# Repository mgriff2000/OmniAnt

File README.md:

# OmniAnt
Repo for the KiCad project for OmniAnt

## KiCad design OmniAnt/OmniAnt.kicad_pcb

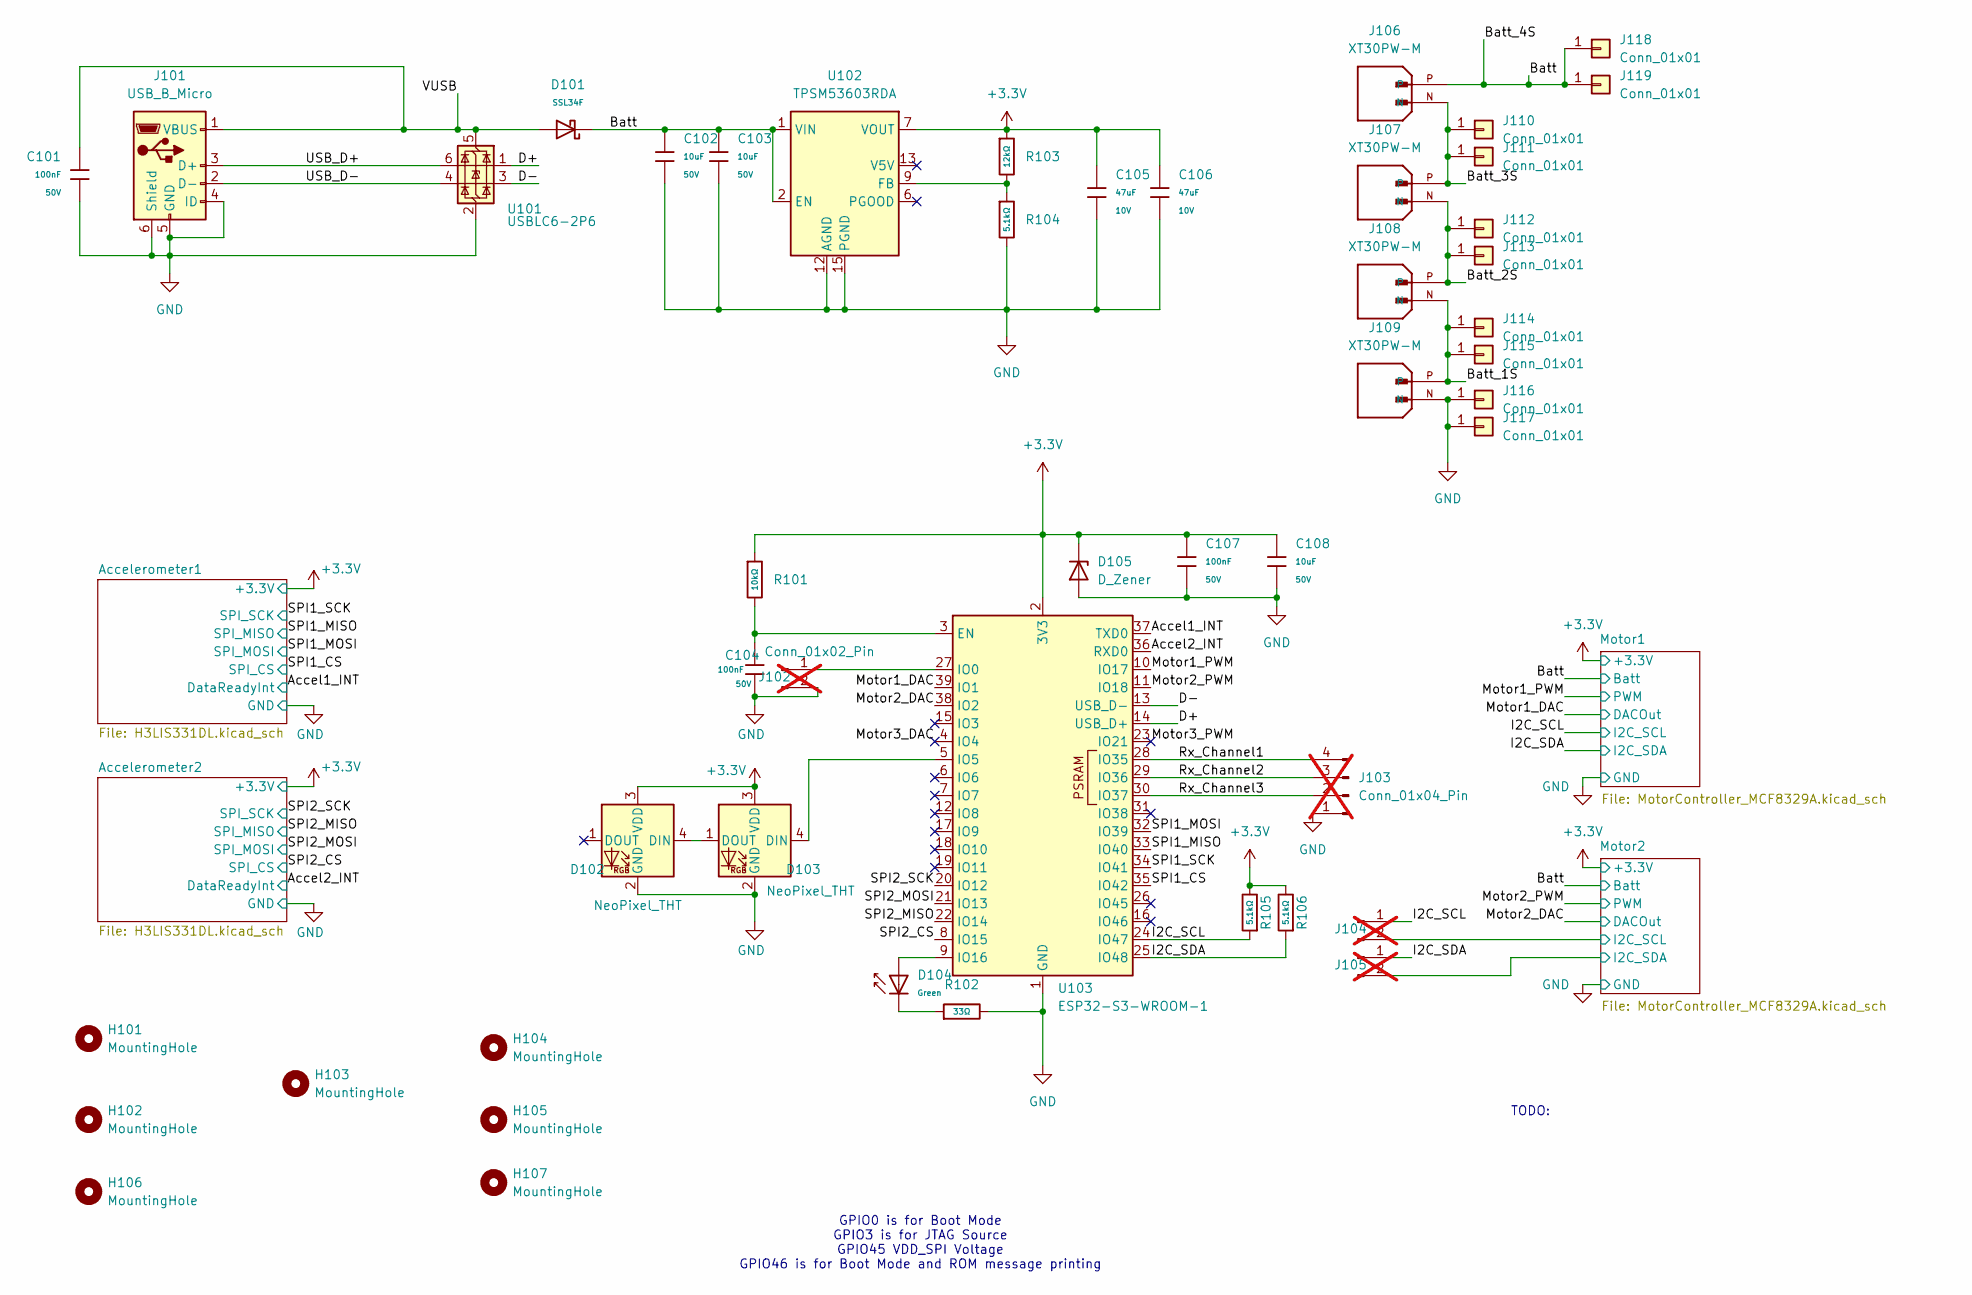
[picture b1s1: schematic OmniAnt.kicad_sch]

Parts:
C101, C104, C107: 100nF; C_0603; Voltage Rated 50V; Tolerance ±10%; Part CC0603KRX7R9BB104; LCSC C14663
C102, C103, C108: 10uF; C_0805; Voltage Rated 50V; Tolerance ±10%; Part GRM21BR61H106KE43L; LCSC C440198
C105, C106: 47uF; C_1206; Voltage Rated 10V; Tolerance ±20%; Part CL31A476MPHNNNE; LCSC C96123
D101: SSL34F; D_SMAF; Part SSL34F; LCSC C28646282
D102, D103: NeoPixel_THT; LED_D5.0mm-4_RGB
D104: Green; D_0805; Part KT-0805G; LCSC C2297
D105: D_Zener; D_SOD-123FL; Manufacturer Part Number SMF3.3; LCSC C2649858
H101, H102, H104, H105, H106, H107: MountingHole; MountingHole_3mm
H103: MountingHole; MountingHole_4.3mm_M4_DIN965
J101: USB_B_Micro; USB_Micro-B_Molex-105017-0001; LCSC C136000
J102, J104, J105: Conn_01x02_Pin; PinHeader_1x02_P1.27mm_Vertical; not fitted
J103: Conn_01x04_Pin; PinHeader_1x04_P2.54mm_Vertical; not fitted
J106, J107, J108, J109: XT30PW-M; AMASS_XT30PW-M; PARTREV 1.2; LCSC C431092
J110, J111, J112, J113, J114, J115, J116, J117, J118, J119: Conn_01x01; SolderWire-1.5sqmm_1x01_D1.7mm_OD3mm
R101: 10kΩ; R_0402; Overload Voltage (Max) 50V; Tolerance ±1%; Part 0402WGF1002TCE; LCSC C25744
R102: 33Ω; R_0402; Overload Voltage (Max) 50V; Tolerance ±1%; Part 0402WGF330JTCE; LCSC C25105
R103: 12kΩ; R_0402; Overload Voltage (Max) 50V; Tolerance ±1%; Part 0402WGF1202TCE; LCSC C25752
R104, R105, R106: 5.1kΩ; R_0402; Overload Voltage (Max) 50V; Tolerance ±1%; Part 0402WGF5101TCE; LCSC C25905
U101: USBLC6-2P6; SOT-666; LCSC C15999
U102: TPSM53603RDA; Texas_B3QFN-14-1EP_5x5.5mm_P0.65mm_ThermalVia; LCSC C2860943
U103: ESP32-S3-WROOM-1; LCSC C2913197

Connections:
+3.3V: C105.1, C106.1, C107.1, C108.1, D102.3 (VDD), D103.3 (VDD), D105.1 (K), R101.1, R103.1, R105.2, R106.2, U102.7 (VOUT), U102.8 (VOUT), U103.2 (3V3); also elsewhere on the board
/Accel1_INT: U103.37 (TXD0); also elsewhere on the board
/Accel2_INT: U103.36 (RXD0); also elsewhere on the board
/Batt: C102.1, C103.1, D101.1, J106.P, J118.1, J119.1, U102.1 (VIN), U102.2 (EN), U102.14 (VIN); also elsewhere on the board
/Batt_1S: J108.N, J109.P, J114.1, J115.1
/Batt_2S: J107.N, J108.P, J112.1, J113.1
/Batt_3S: J106.N, J107.P, J110.1, J111.1
/D+: U101.1 (I/O1), U103.14 (USB_D+)
/D-: U101.3 (I/O2), U103.13 (USB_D-)
/I2C_SCL: J104.1, R105.1, U103.24 (IO47); also elsewhere on the board
/I2C_SDA: J105.1, R106.1, U103.25 (IO48); also elsewhere on the board
/Motor1_DAC: U103.39 (IO1); also elsewhere on the board
/Motor1_PWM: U103.10 (IO17); also elsewhere on the board
/Motor2/I2C_SCL: J104.2; also elsewhere on the board
/Motor2/I2C_SDA: J105.2; also elsewhere on the board
/Motor2_DAC: U103.38 (IO2); also elsewhere on the board
/Motor2_PWM: U103.11 (IO18); also elsewhere on the board
/Motor3_DAC: U103.4 (IO4)
/Motor3_PWM: U103.23 (IO21)
/Rx_Channel1: J103.4, U103.28 (IO35)
/Rx_Channel2: J103.3, U103.29 (IO36)
/Rx_Channel3: J103.2, U103.30 (IO37)
/SPI1_CS: U103.35 (IO42); also elsewhere on the board
/SPI1_MISO: U103.33 (IO40); also elsewhere on the board
/SPI1_MOSI: U103.32 (IO39); also elsewhere on the board
/SPI1_SCK: U103.34 (IO41); also elsewhere on the board
/SPI2_CS: U103.8 (IO15); also elsewhere on the board
/SPI2_MISO: U103.22 (IO14); also elsewhere on the board
/SPI2_MOSI: U103.21 (IO13); also elsewhere on the board
/SPI2_SCK: U103.20 (IO12); also elsewhere on the board
/USB_D+: J101.3 (D+), U101.6 (I/O1)
/USB_D-: J101.2 (D-), U101.4 (I/O2)
/VUSB: C101.1, D101.2, J101.1 (VBUS), U101.5 (VBUS)
GND: C101.2, C102.2, C103.2, C104.2, C105.2, C106.2, C107.2, C108.2, D102.2 (GND), D103.2 (GND), D105.2 (A), J101.4 (ID), J101.5 (GND), J101.6 (Shield), J102.2, J103.1, J109.N, J116.1, J117.1, R102.2, R104.2, U101.2 (GND), U102.3 (PGND), U102.10 (PGND), U102.11 (PGND), U102.12 (AGND), U102.15 (PGND), U103.1 (GND), U103.40 (GND), U103.41 (GND); also elsewhere on the board
unnamed: D102.4 (DIN), D103.1 (DOUT)
unnamed: D103.4 (DIN), U103.5 (IO5)
unnamed: D104.1, R102.1
unnamed: J102.1, U103.27 (IO0)
unnamed: R103.2, R104.1, U102.9 (FB)
unnamed: C104.1, R101.2, U103.3 (EN)
unnamed: D104.2, U103.9 (IO16)

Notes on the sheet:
TODO:
GPIO0 is for Boot Mode GPIO3 is for JTAG Source GPIO45 VDD_SPI Voltage GPIO46 is for Boot Mode and ROM message printing

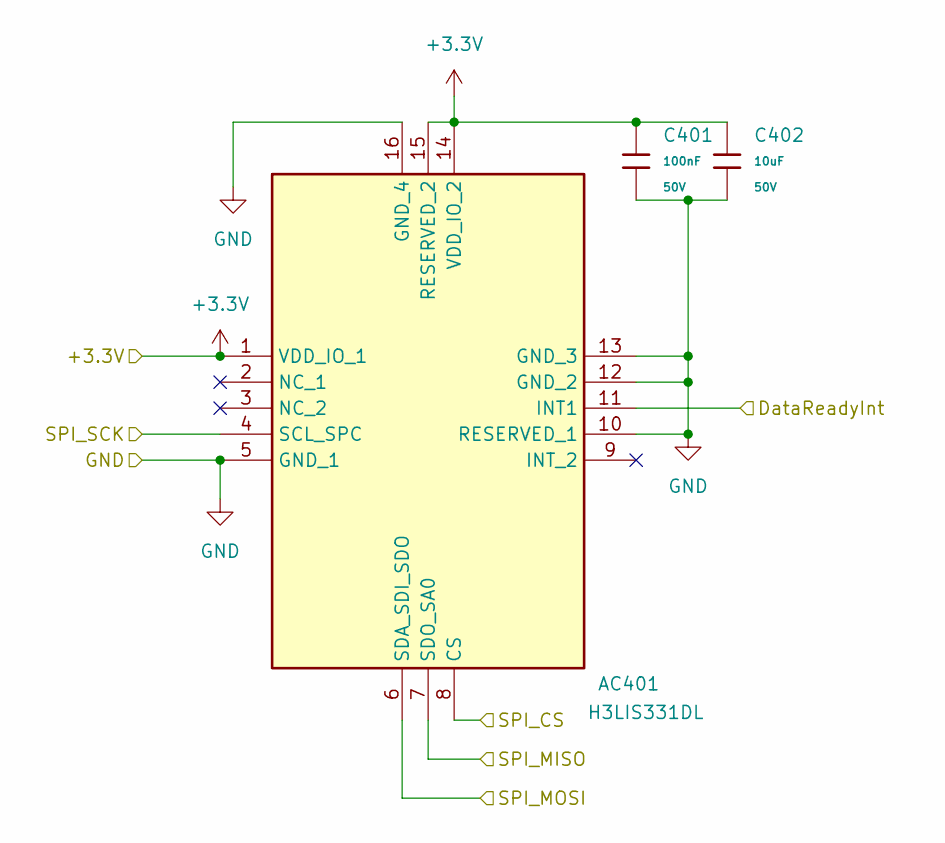
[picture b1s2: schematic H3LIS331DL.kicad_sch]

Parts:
AC401: H3LIS331DL; LIS3DHTR; Manufacturer_Part_Number H3LIS331DL; Mouser Part Number 511-H3LIS331DL
C401: 100nF; C_0603; Voltage Rated 50V; Tolerance ±10%; Part CC0603KRX7R9BB104; LCSC C14663
C402: 10uF; C_0805; Voltage Rated 50V; Tolerance ±10%; Part GRM21BR61H106KE43L; LCSC C440198

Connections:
+3.3V: AC401.1 (VDD_IO_1), AC401.14 (VDD_IO_2), AC401.15 (RESERVED_2), C401.1, C402.1; also elsewhere on the board
/Accel1_INT: AC401.11 (INT1); also elsewhere on the board
/SPI1_CS: AC401.8 (CS); also elsewhere on the board
/SPI1_MISO: AC401.7 (SDO_SA0); also elsewhere on the board
/SPI1_MOSI: AC401.6 (SDA_SDI_SDO); also elsewhere on the board
/SPI1_SCK: AC401.4 (SCL_SPC); also elsewhere on the board
GND: AC401.5 (GND_1), AC401.10 (RESERVED_1), AC401.12 (GND_2), AC401.13 (GND_3), AC401.16 (GND_4), C401.2, C402.2; also elsewhere on the board

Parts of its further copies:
AC501: H3LIS331DL; LIS3DHTR; Manufacturer_Part_Number H3LIS331DL; Mouser Part Number 511-H3LIS331DL
C501: 100nF; C_0603; Voltage Rated 50V; Tolerance ±10%; Part CC0603KRX7R9BB104; LCSC C14663
C502: 10uF; C_0805; Voltage Rated 50V; Tolerance ±10%; Part GRM21BR61H106KE43L; LCSC C440198

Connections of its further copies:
+3.3V: AC501.1 (VDD_IO_1), AC501.14 (VDD_IO_2), AC501.15 (RESERVED_2), C501.1, C502.1; also elsewhere on the board
/Accel2_INT: AC501.11 (INT1); also elsewhere on the board
/SPI2_CS: AC501.8 (CS); also elsewhere on the board
/SPI2_MISO: AC501.7 (SDO_SA0); also elsewhere on the board
/SPI2_MOSI: AC501.6 (SDA_SDI_SDO); also elsewhere on the board
/SPI2_SCK: AC501.4 (SCL_SPC); also elsewhere on the board
GND: AC501.5 (GND_1), AC501.10 (RESERVED_1), AC501.12 (GND_2), AC501.13 (GND_3), AC501.16 (GND_4), C501.2, C502.2; also elsewhere on the board

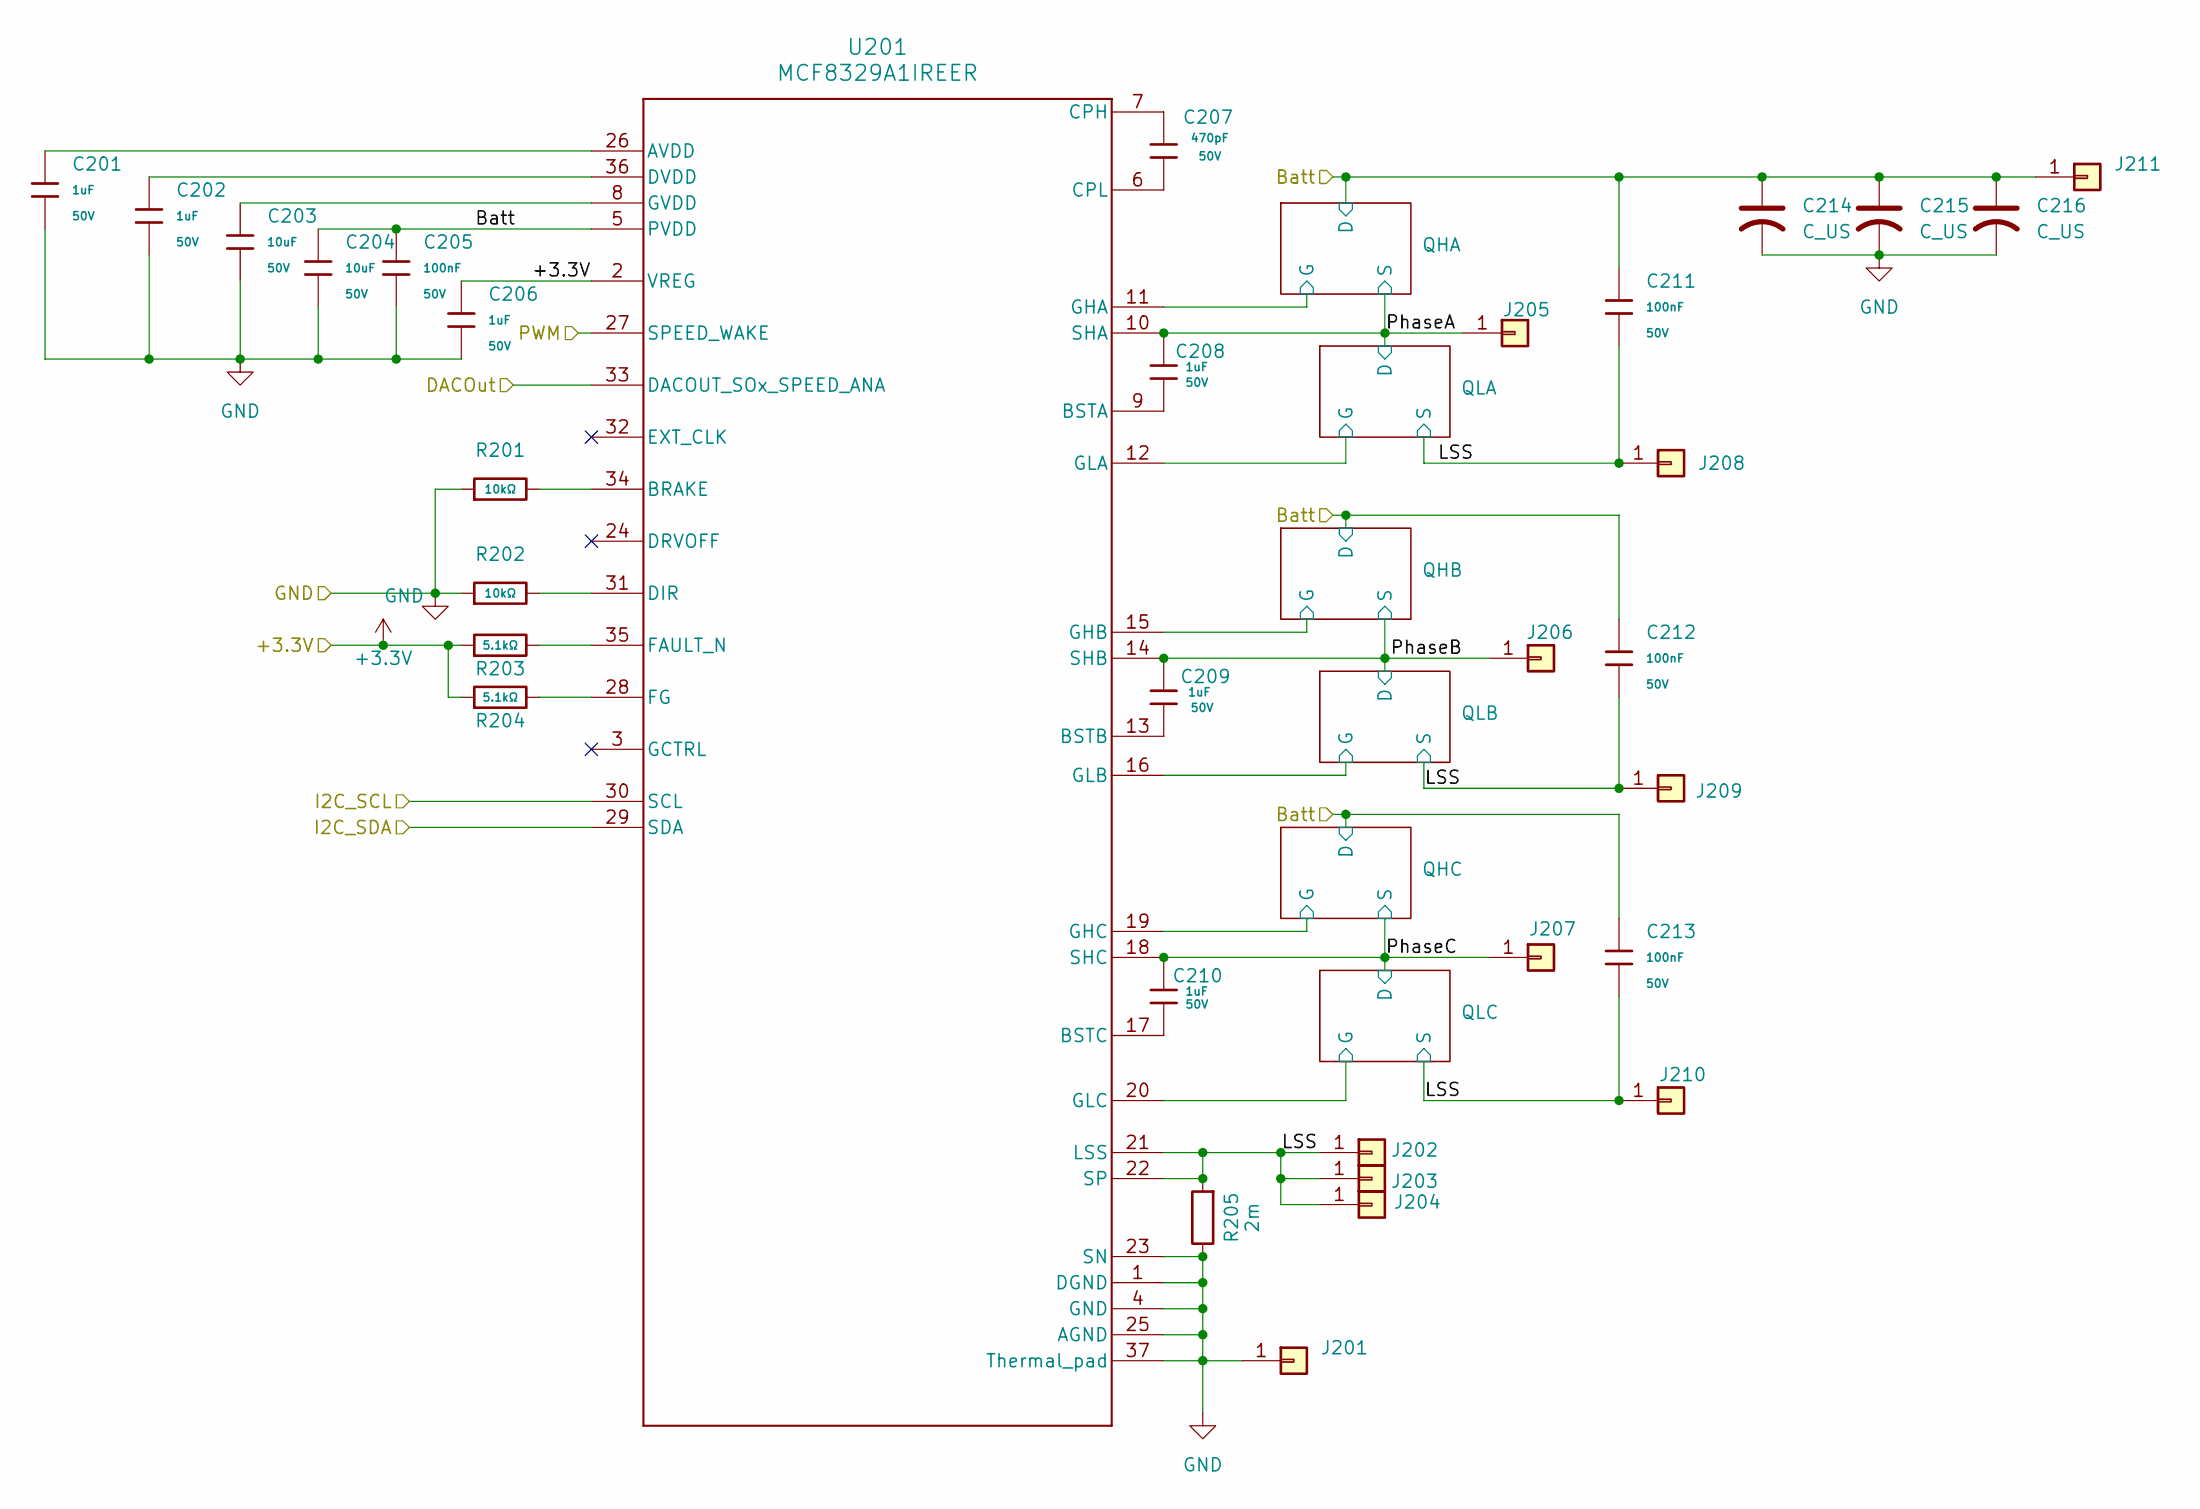
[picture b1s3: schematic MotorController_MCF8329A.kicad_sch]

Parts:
C201, C202, C206, C208, C209, C210: 1uF; C_0603; Voltage Rated 50V; Tolerance ±10%; Part CL10A105KB8NNNC; LCSC C15849
C203, C204: 10uF; C_0805; Voltage Rated 50V; Tolerance ±10%; Part GRM21BR61H106KE43L; LCSC C440198
C205, C211, C212, C213: 100nF; C_0603; Voltage Rated 50V; Tolerance ±10%; Part CC0603KRX7R9BB104; LCSC C14663
C207: 470pF; C_0603; Voltage Rated 50V; Tolerance ±10%; Part 0603B471K500NT; LCSC C1620
C214: C_US; CP_Radial_D6.3mm_P2.50mm; Manufacturer Part Number HT1E227M0607PC
C215, C216: C_US; CP_Radial_D6.3mm_P2.50mm
J201, J211: Conn_01x01; SolderWire-1.5sqmm_1x01_D1.7mm_OD3mm
J202, J203, J204, J205, J206, J207, J208, J209, J210: Conn_01x01; SolderWire-0.25sqmm_1x01_D0.65mm_OD1.7mm
R201, R202: 10kΩ; R_0402; Overload Voltage (Max) 50V; Tolerance ±1%; Part 0402WGF1002TCE; LCSC C25744
R203, R204: 5.1kΩ; R_0402; Overload Voltage (Max) 50V; Tolerance ±1%; Part 0402WGF5101TCE; LCSC C25905
R205: 2m; R_1206_3216Metric
U201: MCF8329A1IREER; REE0036A-MFG

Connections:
+3.3V: C206.1, R203.1, R204.1, U201.2 (VREG); also elsewhere on the board
/Batt: C204.1, C205.1, C211.1, C212.1, C213.1, C214.1, C215.1, C216.1, J211.1, U201.5 (PVDD); also elsewhere on the board
/I2C_SCL: U201.30 (SCL); also elsewhere on the board
/I2C_SDA: U201.29 (SDA); also elsewhere on the board
/Motor1/LSS: C211.2, C212.2, C213.2, J202.1, J203.1, J204.1, J208.1, J209.1, J210.1, R205.2, U201.21 (LSS), U201.22 (SP); also elsewhere on the board
/Motor1/PhaseA: C208.1, J205.1, U201.10 (SHA); also elsewhere on the board
/Motor1/PhaseB: C209.1, J206.1, U201.14 (SHB); also elsewhere on the board
/Motor1/PhaseC: C210.1, J207.1, U201.18 (SHC); also elsewhere on the board
/Motor1/QHA/G: U201.11 (GHA); also elsewhere on the board
/Motor1/QHB/G: U201.15 (GHB); also elsewhere on the board
/Motor1/QHC/G: U201.19 (GHC); also elsewhere on the board
/Motor1/QLA/G: U201.12 (GLA); also elsewhere on the board
/Motor1/QLB/G: U201.16 (GLB); also elsewhere on the board
/Motor1/QLC/G: U201.20 (GLC); also elsewhere on the board
/Motor1_DAC: U201.33 (DACOUT_SOx_SPEED_ANA); also elsewhere on the board
/Motor1_PWM: U201.27 (SPEED_WAKE); also elsewhere on the board
GND: C201.2, C202.2, C203.2, C204.2, C205.2, C206.2, C214.2, C215.2, C216.2, J201.1, R201.1, R202.1, R205.1, U201.1 (DGND), U201.4 (GND), U201.23 (SN), U201.25 (AGND), U201.37 (Thermal_pad), U201.38, U201.39, U201.40, U201.41, U201.42, U201.43, U201.44, U201.45; also elsewhere on the board
unnamed: C201.1, U201.26 (AVDD)
unnamed: R201.2, U201.34 (BRAKE)
unnamed: C208.2, U201.9 (BSTA)
unnamed: C209.2, U201.13 (BSTB)
unnamed: C210.2, U201.17 (BSTC)
unnamed: C207.1, U201.7 (CPH)
unnamed: C207.2, U201.6 (CPL)
unnamed: R202.2, U201.31 (DIR)
unnamed: C202.1, U201.36 (DVDD)
unnamed: R203.2, U201.35 (FAULT_N)
unnamed: R204.2, U201.28 (FG)
unnamed: C203.1, U201.8 (GVDD)

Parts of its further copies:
C301, C302, C306, C308, C309, C310: 1uF; C_0603; Voltage Rated 50V; Tolerance ±10%; Part CL10A105KB8NNNC; LCSC C15849
C303, C304: 10uF; C_0805; Voltage Rated 50V; Tolerance ±10%; Part GRM21BR61H106KE43L; LCSC C440198
C305, C311, C312, C313: 100nF; C_0603; Voltage Rated 50V; Tolerance ±10%; Part CC0603KRX7R9BB104; LCSC C14663
C307: 470pF; C_0603; Voltage Rated 50V; Tolerance ±10%; Part 0603B471K500NT; LCSC C1620
C314: C_US; CP_Radial_D6.3mm_P2.50mm; Manufacturer Part Number HT1E227M0607PC
C315, C316: C_US; CP_Radial_D6.3mm_P2.50mm
J301, J311: Conn_01x01; SolderWire-1.5sqmm_1x01_D1.7mm_OD3mm
J302, J303, J304, J305, J306, J307, J308, J309, J310: Conn_01x01; SolderWire-0.25sqmm_1x01_D0.65mm_OD1.7mm
R301, R302: 10kΩ; R_0402; Overload Voltage (Max) 50V; Tolerance ±1%; Part 0402WGF1002TCE; LCSC C25744
R303, R304: 5.1kΩ; R_0402; Overload Voltage (Max) 50V; Tolerance ±1%; Part 0402WGF5101TCE; LCSC C25905
R305: 2m; R_1206_3216Metric
U301: MCF8329A1IREER; REE0036A-MFG

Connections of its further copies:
+3.3V: C306.1, R303.1, R304.1, U301.2 (VREG); also elsewhere on the board
/Batt: C304.1, C305.1, C311.1, C312.1, C313.1, C314.1, C315.1, C316.1, J311.1, U301.5 (PVDD); also elsewhere on the board
/Motor2/I2C_SCL: U301.30 (SCL); also elsewhere on the board
/Motor2/I2C_SDA: U301.29 (SDA); also elsewhere on the board
/Motor2/LSS: C311.2, C312.2, C313.2, J302.1, J303.1, J304.1, J308.1, J309.1, J310.1, R305.2, U301.21 (LSS), U301.22 (SP); also elsewhere on the board
/Motor2/PhaseA: C308.1, J305.1, U301.10 (SHA); also elsewhere on the board
/Motor2/PhaseB: C309.1, J306.1, U301.14 (SHB); also elsewhere on the board
/Motor2/PhaseC: C310.1, J307.1, U301.18 (SHC); also elsewhere on the board
/Motor2/QHA/G: U301.11 (GHA); also elsewhere on the board
/Motor2/QHB/G: U301.15 (GHB); also elsewhere on the board
/Motor2/QHC/G: U301.19 (GHC); also elsewhere on the board
/Motor2/QLA/G: U301.12 (GLA); also elsewhere on the board
/Motor2/QLB/G: U301.16 (GLB); also elsewhere on the board
/Motor2/QLC/G: U301.20 (GLC); also elsewhere on the board
/Motor2_DAC: U301.33 (DACOUT_SOx_SPEED_ANA); also elsewhere on the board
/Motor2_PWM: U301.27 (SPEED_WAKE); also elsewhere on the board
GND: C301.2, C302.2, C303.2, C304.2, C305.2, C306.2, C314.2, C315.2, C316.2, J301.1, R301.1, R302.1, R305.1, U301.1 (DGND), U301.4 (GND), U301.23 (SN), U301.25 (AGND), U301.37 (Thermal_pad), U301.38, U301.39, U301.40, U301.41, U301.42, U301.43, U301.44, U301.45; also elsewhere on the board
unnamed: C301.1, U301.26 (AVDD)
unnamed: R301.2, U301.34 (BRAKE)
unnamed: C308.2, U301.9 (BSTA)
unnamed: C309.2, U301.13 (BSTB)
unnamed: C310.2, U301.17 (BSTC)
unnamed: C307.1, U301.7 (CPH)
unnamed: C307.2, U301.6 (CPL)
unnamed: R302.2, U301.31 (DIR)
unnamed: C302.1, U301.36 (DVDD)
unnamed: R303.2, U301.35 (FAULT_N)
unnamed: R304.2, U301.28 (FG)
unnamed: C303.1, U301.8 (GVDD)

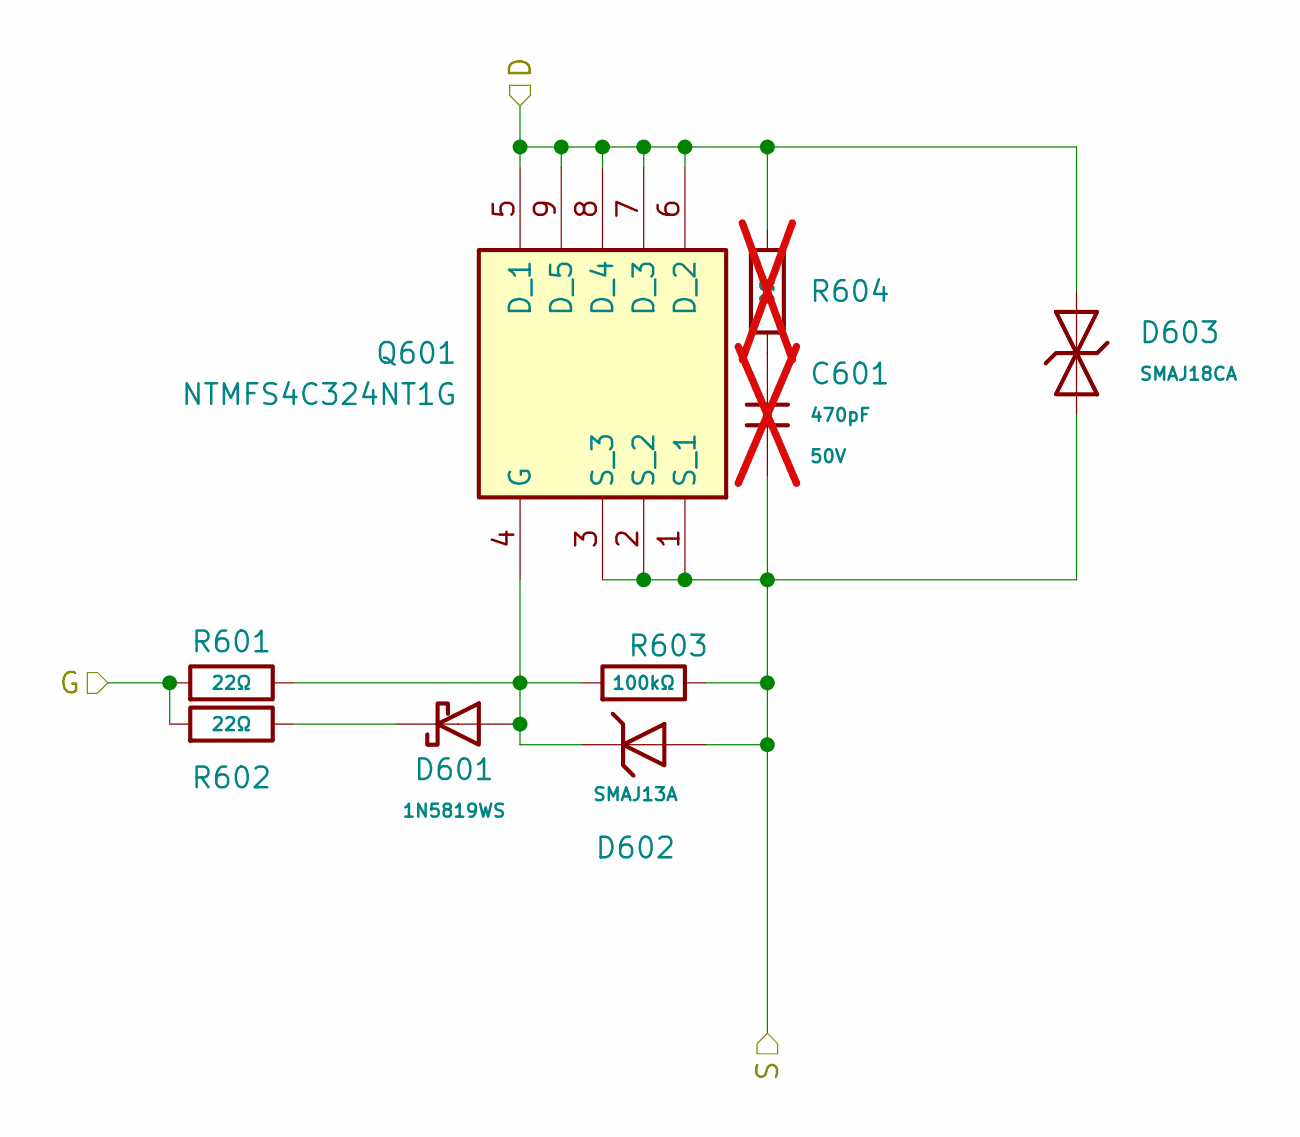
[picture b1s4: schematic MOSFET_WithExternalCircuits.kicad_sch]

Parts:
C601: 470pF; C_0603; Voltage Rated 50V; Tolerance ±10%; Part 0603B471K500NT; LCSC C1620; not fitted
D601: 1N5819WS; D_SOD-323; Forward Voltage (Vf@If) 600mV@1A; Reverse Voltage (Vr) 40V; Part 1N5819WS; LCSC C191023
D602: SMAJ13A; D_SMA; Part SMAJ13A; LCSC C19077533
D603: SMAJ18CA; D_SMA; Part SMAJ18CA; LCSC C19077539
Q601: NTMFS4C324NT1G; NVMFS5C442NLWFAFT1G; Mouser Part Number 863-NTMFS4C324NT1G
R601, R602: 22Ω; R_0805; Overload Voltage (Max) 150V; Tolerance ±1%; Part 0805W8F220JT5E; LCSC C17561
R603: 100kΩ; R_0402; Overload Voltage (Max) 50V; Tolerance ±1%; Part 0402WGF1003TCE; LCSC C25741
R604: 0Ω; R_0603; Overload Voltage (Max) 75V; Tolerance ±1%; Part 0603WAF0000T5E; LCSC C21189; not fitted

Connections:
/Motor1/LSS: C601.2, D602.2, D603.1, Q601.1 (S_1), Q601.2 (S_2), Q601.3 (S_3), R603.2; also elsewhere on the board
/Motor1/PhaseA: D603.2, Q601.5 (D_1), Q601.6 (D_2), Q601.7 (D_3), Q601.8 (D_4), Q601.9 (D_5), R604.1; also elsewhere on the board
/Motor1/QLA/G: R601.1, R602.1; also elsewhere on the board
unnamed: C601.1, R604.2
unnamed: D601.1, R602.2
unnamed: D601.2, D602.1, Q601.4 (G), R601.2, R603.1

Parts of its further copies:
C701, C801, C901, C1001, C1101, C1201, C1301, C1401, C1501, C1601, C1701: 470pF; C_0603; Voltage Rated 50V; Tolerance ±10%; Part 0603B471K500NT; LCSC C1620; not fitted
D701, D801, D901, D1001, D1101, D1201, D1301, D1401, D1501, D1601, D1701: 1N5819WS; D_SOD-323; Forward Voltage (Vf@If) 600mV@1A; Reverse Voltage (Vr) 40V; Part 1N5819WS; LCSC C191023
D702, D802, D902, D1002, D1102, D1202, D1302, D1402, D1502, D1602, D1702: SMAJ13A; D_SMA; Part SMAJ13A; LCSC C19077533
D703, D803, D903, D1003, D1103, D1203, D1303, D1403, D1503, D1603, D1703: SMAJ18CA; D_SMA; Part SMAJ18CA; LCSC C19077539
Q701, Q801, Q901, Q1001, Q1101, Q1201, Q1301, Q1401, Q1501, Q1601, Q1701: NTMFS4C324NT1G; NVMFS5C442NLWFAFT1G; Mouser Part Number 863-NTMFS4C324NT1G
R701, R702, R801, R802, R901, R902, R1001, R1002, R1101, R1102, R1201, R1202, R1301, R1302, R1401, R1402, R1501, R1502, R1601, R1602, R1701, R1702: 22Ω; R_0805; Overload Voltage (Max) 150V; Tolerance ±1%; Part 0805W8F220JT5E; LCSC C17561
R703, R803, R903, R1003, R1103, R1203, R1303, R1403, R1503, R1603, R1703: 100kΩ; R_0402; Overload Voltage (Max) 50V; Tolerance ±1%; Part 0402WGF1003TCE; LCSC C25741
R704, R804, R904, R1004, R1104, R1204, R1304, R1404, R1504, R1604, R1704: 0Ω; R_0603; Overload Voltage (Max) 75V; Tolerance ±1%; Part 0603WAF0000T5E; LCSC C21189; not fitted

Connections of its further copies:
/Batt: D703.2, D803.2, D1003.2, D1203.2, D1403.2, D1603.2, Q701.5 (D_1), Q701.6 (D_2), Q701.7 (D_3), Q701.8 (D_4), Q701.9 (D_5), Q801.5 (D_1), Q801.6 (D_2), Q801.7 (D_3), Q801.8 (D_4), Q801.9 (D_5), Q1001.5 (D_1), Q1001.6 (D_2), Q1001.7 (D_3), Q1001.8 (D_4), Q1001.9 (D_5), Q1201.5 (D_1), Q1201.6 (D_2), Q1201.7 (D_3), Q1201.8 (D_4), Q1201.9 (D_5), Q1401.5 (D_1), Q1401.6 (D_2), Q1401.7 (D_3), Q1401.8 (D_4), Q1401.9 (D_5), Q1601.5 (D_1), Q1601.6 (D_2), Q1601.7 (D_3), Q1601.8 (D_4), Q1601.9 (D_5), R704.1, R804.1, R1004.1, R1204.1, R1404.1, R1604.1; also elsewhere on the board
/Motor1/LSS: C901.2, C1301.2, D902.2, D903.1, D1302.2, D1303.1, Q901.1 (S_1), Q901.2 (S_2), Q901.3 (S_3), Q1301.1 (S_1), Q1301.2 (S_2), Q1301.3 (S_3), R903.2, R1303.2; also elsewhere on the board
/Motor1/PhaseA: C701.2, D702.2, D703.1, Q701.1 (S_1), Q701.2 (S_2), Q701.3 (S_3), R703.2; also elsewhere on the board
/Motor1/PhaseB: C1001.2, D903.2, D1002.2, D1003.1, Q901.5 (D_1), Q901.6 (D_2), Q901.7 (D_3), Q901.8 (D_4), Q901.9 (D_5), Q1001.1 (S_1), Q1001.2 (S_2), Q1001.3 (S_3), R904.1, R1003.2; also elsewhere on the board
/Motor1/PhaseC: C1401.2, D1303.2, D1402.2, D1403.1, Q1301.5 (D_1), Q1301.6 (D_2), Q1301.7 (D_3), Q1301.8 (D_4), Q1301.9 (D_5), Q1401.1 (S_1), Q1401.2 (S_2), Q1401.3 (S_3), R1304.1, R1403.2; also elsewhere on the board
/Motor1/QHA/G: R701.1, R702.1; also elsewhere on the board
/Motor1/QHB/G: R1001.1, R1002.1; also elsewhere on the board
/Motor1/QHC/G: R1401.1, R1402.1; also elsewhere on the board
/Motor1/QLB/G: R901.1, R902.1; also elsewhere on the board
/Motor1/QLC/G: R1301.1, R1302.1; also elsewhere on the board
/Motor2/LSS: C1101.2, C1501.2, C1701.2, D1102.2, D1103.1, D1502.2, D1503.1, D1702.2, D1703.1, Q1101.1 (S_1), Q1101.2 (S_2), Q1101.3 (S_3), Q1501.1 (S_1), Q1501.2 (S_2), Q1501.3 (S_3), Q1701.1 (S_1), Q1701.2 (S_2), Q1701.3 (S_3), R1103.2, R1503.2, R1703.2; also elsewhere on the board
/Motor2/PhaseA: C801.2, D802.2, D803.1, D1703.2, Q801.1 (S_1), Q801.2 (S_2), Q801.3 (S_3), Q1701.5 (D_1), Q1701.6 (D_2), Q1701.7 (D_3), Q1701.8 (D_4), Q1701.9 (D_5), R803.2, R1704.1; also elsewhere on the board
/Motor2/PhaseB: C1201.2, D1103.2, D1202.2, D1203.1, Q1101.5 (D_1), Q1101.6 (D_2), Q1101.7 (D_3), Q1101.8 (D_4), Q1101.9 (D_5), Q1201.1 (S_1), Q1201.2 (S_2), Q1201.3 (S_3), R1104.1, R1203.2; also elsewhere on the board
/Motor2/PhaseC: C1601.2, D1503.2, D1602.2, D1603.1, Q1501.5 (D_1), Q1501.6 (D_2), Q1501.7 (D_3), Q1501.8 (D_4), Q1501.9 (D_5), Q1601.1 (S_1), Q1601.2 (S_2), Q1601.3 (S_3), R1504.1, R1603.2; also elsewhere on the board
/Motor2/QHA/G: R801.1, R802.1; also elsewhere on the board
/Motor2/QHB/G: R1201.1, R1202.1; also elsewhere on the board
/Motor2/QHC/G: R1601.1, R1602.1; also elsewhere on the board
/Motor2/QLA/G: R1701.1, R1702.1; also elsewhere on the board
/Motor2/QLB/G: R1101.1, R1102.1; also elsewhere on the board
/Motor2/QLC/G: R1501.1, R1502.1; also elsewhere on the board
unnamed: C701.1, R704.2
unnamed: C801.1, R804.2
unnamed: C901.1, R904.2
unnamed: C1001.1, R1004.2
unnamed: C1101.1, R1104.2
unnamed: C1201.1, R1204.2
unnamed: C1301.1, R1304.2
unnamed: C1401.1, R1404.2
unnamed: C1501.1, R1504.2
unnamed: C1601.1, R1604.2
unnamed: C1701.1, R1704.2
unnamed: D701.1, R702.2
unnamed: D801.1, R802.2
unnamed: D901.1, R902.2
unnamed: D1001.1, R1002.2
unnamed: D1101.1, R1102.2
unnamed: D1201.1, R1202.2
unnamed: D1301.1, R1302.2
unnamed: D1401.1, R1402.2
unnamed: D1501.1, R1502.2
unnamed: D1601.1, R1602.2
unnamed: D1701.1, R1702.2
unnamed: D701.2, D702.1, Q701.4 (G), R701.2, R703.1
unnamed: D801.2, D802.1, Q801.4 (G), R801.2, R803.1
unnamed: D901.2, D902.1, Q901.4 (G), R901.2, R903.1
unnamed: D1001.2, D1002.1, Q1001.4 (G), R1001.2, R1003.1
unnamed: D1101.2, D1102.1, Q1101.4 (G), R1101.2, R1103.1
unnamed: D1201.2, D1202.1, Q1201.4 (G), R1201.2, R1203.1
unnamed: D1301.2, D1302.1, Q1301.4 (G), R1301.2, R1303.1
unnamed: D1401.2, D1402.1, Q1401.4 (G), R1401.2, R1403.1
unnamed: D1501.2, D1502.1, Q1501.4 (G), R1501.2, R1503.1
unnamed: D1601.2, D1602.1, Q1601.4 (G), R1601.2, R1603.1
unnamed: D1701.2, D1702.1, Q1701.4 (G), R1701.2, R1703.1

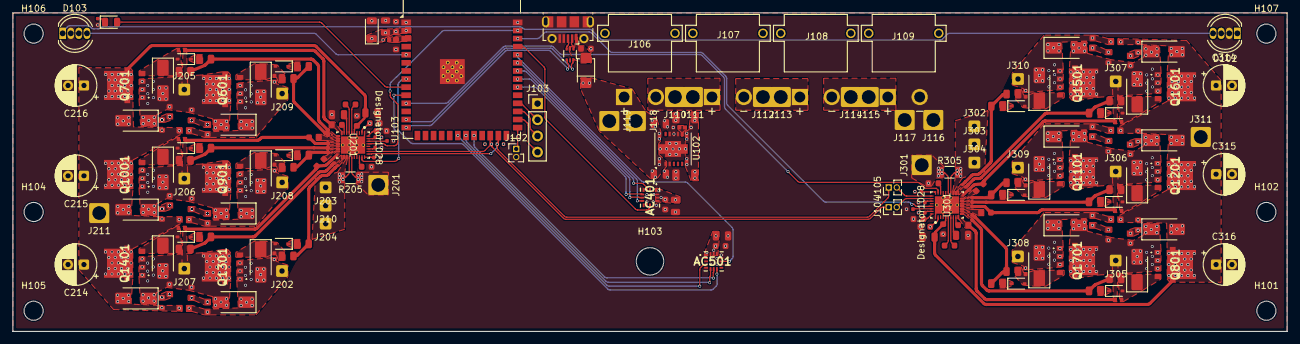
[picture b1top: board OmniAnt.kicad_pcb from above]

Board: 4 copper layers, 200.0 x 50.0 mm, 228 parts (0 on the bottom side), 119 nets.

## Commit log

2025-05-24 First Test Commit
2025-05-24 First commit through KiCad
2025-05-27 I dropped in the esp, DCDC, diode, and usb connector.
2025-06-10 Added a schematic for the motor controller.
2025-06-13 Mostly organizing
2025-06-13 Good progress on the power stage today.
2025-06-16 I added a green LED.
2025-06-16 I added in addressable LEDs, the accelerometers, and some inputs from a receiver just in case.
2025-06-27 I added in the XT30 Connectors for the batteries
2025-06-30 Adding the design rules for JLCPCB and added the jlcpcb to the ignore list.
2025-07-01 added a link to the motor controller datasheet and changed the connector footprint for the RC interface.
2025-07-07 fixed all the schematic errors.
2025-07-11 I started to work on the rough placement.
2025-07-16 Major progress on the motor driver layout. Lots of learning with how to draw traces and pours.
2025-07-17 I made more progress on the layout. I'm working on adding the extra protection components to the driver circuit.
2025-07-18 Ok I did a lot of reading today. I'm going to split each FET into a sheet, so I can add the external circuitry more easily.
    I may need to source a different FET. The one I selected has a good EAS, but the rating is only for 11A. and Ideally I would be able to do 19 or 20A. I'm sure I will never do that much current , but 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
2025-07-20 I got the mosfets in as a separate sheet and selected the additional protection circuitry. I'm working on finding the other recommended capacitors now.
2025-07-21 Well shit making the FETs into libraries totally screwed up the annotation :( I decided to just redo the layout for the FETs anyhow.
2025-07-23 Really good progress today. I got all the FETs placed again and routed. I'm working on the pours for the FETs now.
2025-08-01 I di some good work breaking out the traces around the gate driver. Unfortunatly when I went to connect the driver upto the FET array I noticed that I needed to reorder where the phase came out. To d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
2025-08-12 Really good progress. I positioned everything, and ran a bunch of signals.
2025-10-02 Everything looks good to me. I'm going to run design checks now. I'm sure it is going to be bad.
2025-11-13 Last Commit At eMatrix.
